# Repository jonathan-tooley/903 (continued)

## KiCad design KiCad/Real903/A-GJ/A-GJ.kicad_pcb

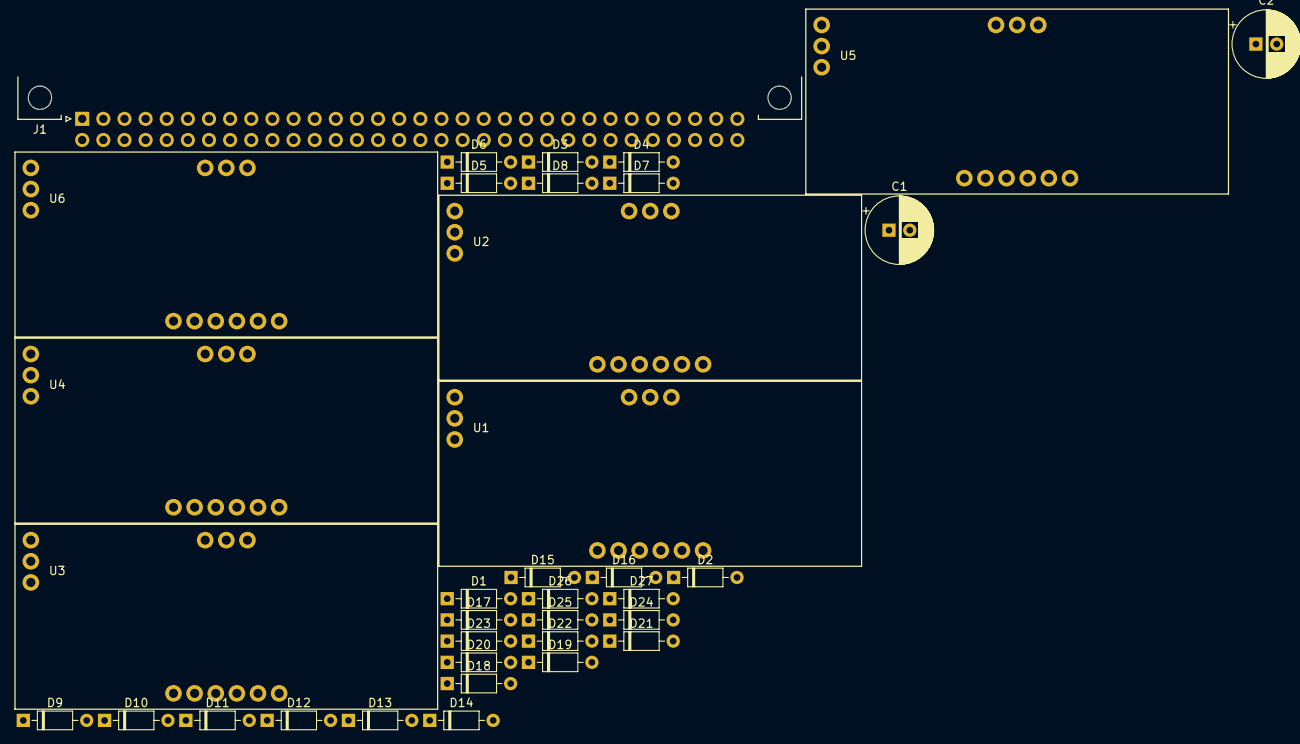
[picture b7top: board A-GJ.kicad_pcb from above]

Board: 2 copper layers, 36 parts (0 on the bottom side), 48 nets, no tracks yet.

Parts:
C1, C2: 6u8; CP_Radial_D8.0mm_P2.50mm
D1, D2, D3, D4, D5, D6, D7, D8, D9, D10, D11, D12, D13, D14, D15, D16, D17, D18, D19, D20, D21, D22, D23, D24, D25, D26, D27: D; D_DO-35_SOD27_P7.62mm_Horizontal
J1: J1; DIN41612_B_2x32_Horizontal
U1: LS03; LSA
U2, U3, U4, U5: LS02; LSA
U6: LS01; LSA

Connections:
2: D1.1, D3.1, D4.1, D6.1, D8.1, D10.1, D12.1, D14.1, D16.1, D18.1, D20.1, D22.1, D23.1, D24.1, D25.1, D26.1, D27.1, U3.11
4: D2.1, D5.1, D7.1, D9.1, D11.1, D13.1, D15.1, D17.1, D19.1, D21.1, U3.13
6v: C2.1, J1.2, J1.B, U1.21, U2.21, U3.21, U4.21, U5.21, U6.21
GND: C1.1, C2.2, J1.1, J1.32, J1.A, J1.AL, U1.22, U2.22, U4.22, U5.22, U6.22
II1m: D1.2, J1.P
II3m: D2.2, D3.2, J1.S
II4m: D4.2, J1.T
II5m: D5.2, D6.2, J1.U
II6m: D7.2, D8.2, J1.V
II7m: D9.2, D10.2, J1.W
II8m: D11.2, D12.2, J1.X
II9m: D13.2, D14.2, J1.Y
II10m: D15.2, D16.2, J1.Z
II11m: D17.2, D18.2, J1.AA
II12m: D19.2, D20.2, J1.AB
II13m: D21.2, D22.2, J1.AC
II14m: D23.2, J1.AD
II15m: D24.2, J1.AE
II16m: D25.2, J1.AF
II17m: D26.2, J1.AH
II18m: D27.2, J1.AJ
IIG: J1.26, U1.6, U1.11, U1.12, U2.1, U6.11, U6.12, U6.13
IIG-: J1.9, U1.13
IIS: J1.8, U2.2
J1': J1.7, U2.5, U3.4
J2-': J1.10, U3.2, U3.5
J3': J1.11, U3.3, U3.6
J3-': J1.C, U1.3
J4-: J1.12, U1.4, U2.3
J5: J1.13, U4.1
J6: J1.14, U4.2
J7: J1.15, U4.3
J8: J1.18, U4.4
J9: J1.19, U4.5
J10: J1.20, U4.6
J11: J1.21, U5.1
J12: J1.22, U5.2
J13: J1.23, U5.3
J14-: J1.24, U5.4
J15-: J1.25, U5.5
J16-: J1.29, U5.6
Neg6v: C1.2, J1.31, J1.AK, U1.23, U2.23, U3.23, U4.23, U5.23, U6.23
unnamed: U1.1, U5.13
unnamed: U2.13, U3.1
unnamed: U4.11, U6.1
unnamed: U4.13, U6.3
unnamed: U5.11, U6.5
U3GND: U2.11, U3.22
